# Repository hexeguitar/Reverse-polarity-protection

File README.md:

# Reverse-polarity-protection
Simple P-MOS based low dropout reverse polarity protection

1. Max input voltage depends on the used P-MOS transistor and the voltage rating of the 10uF cap.
2. Output supply capacitors are optional.
3. If the polyfuse is not used, put a blob of solder on the jumper pads to bypass it.  

### Files:
1. KiCad 5 project.
2. Schematic as PDF
3. html BOM file.

___
(c) 2020 by Piotr Zapart  
www.hexefx.com

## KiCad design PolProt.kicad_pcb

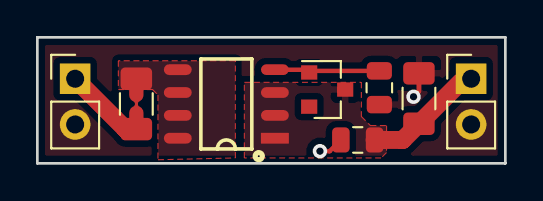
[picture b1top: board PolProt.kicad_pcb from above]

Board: 2 copper layers, 26.0 x 7.0 mm, 9 parts (0 on the bottom side), 5 nets.

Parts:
C1: 10u; C_1206_3216Metric
C2: 100n; C_0805_2012Metric
D1: BZX84C9V1; D_SOT-23_ANK
F1: 100mA; Fuse_1206_3216Metric
J1, J2: VTG; PinHeader_1x02_P2.54mm_Vertical
JP1: FuseBypass; NetTie-2_SMD_Pad0.5mm
Q1: Q_PMOS_SO8; SOIC8
R1: 100k; R_0805_2012Metric

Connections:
/PWR_F: F1.1, JP1.2, Q1.5, Q1.6, Q1.7, Q1.8
/VTG: C1.1, C2.1, D1.1, J2.1, Q1.1, Q1.2, Q1.3
GND: C1.2, C2.2, J1.2, J2.2, R1.2
unnamed: D1.2, Q1.4, R1.1
unnamed: F1.2, J1.1, JP1.1

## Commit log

2020-02-18 readme update
